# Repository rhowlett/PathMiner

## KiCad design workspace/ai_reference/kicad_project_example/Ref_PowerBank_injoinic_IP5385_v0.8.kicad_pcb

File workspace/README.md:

<!-- v0.1 -->
# PathMiner

DC resistance analysis for KiCad PCBs. Reads a `.kicad_pcb` — stackup, tracks, arcs, vias,
pads, filled zones — and answers *"what is the resistance from this pad to that pad, and does
the design pass?"*

It traces real routed copper into a resistor network, derives via barrel spans from the layers
that actually land on them (never from the via's declared layers), models stitched pours as
either a fast 1-D ladder or a rasterised mesh, and solves the whole net by nodal analysis so
parallel copper counts. Output is point-to-point resistance, voltage drop, endpoint voltage and
temperature rise, in Markdown, text, PDF or JSON, driven by a schema-validated JSON
net-selection file so the same audit re-runs from the CLI against every board revision.

## Status

**Working application, pre-split.** All functionality currently lives in the single file
`tools/pcb_trace_resistance.py` (v0.13, 5546 lines). The package folders `core/`, `ui/`,
`tests/` and `schema/` are scaffolded but empty; the split is designed in
`documents/library_refactor_recommendations.md` and has not been executed.

| Selftest | Result |
|---|---|
| Reference test board | 254 / 254 |
| Real 4-layer power bank | 284 / 284 |
| Headless, no board | 118 / 118 |

## Running it

```bash
python3 tools/pcb_trace_resistance.py                       # GUI
python3 tools/pcb_trace_resistance.py board.kicad_pcb       # GUI, board preloaded

python3 tools/pcb_trace_resistance.py --selftest [board.kicad_pcb]
python3 tools/pcb_trace_resistance.py --dump-stackup board.kicad_pcb [--plating 25] [--outer-plating]
python3 tools/pcb_trace_resistance.py --emit-schema [file.json]
python3 tools/pcb_trace_resistance.py --emit-nets board.kicad_pcb --out sel.json
python3 tools/pcb_trace_resistance.py --report board.kicad_pcb --nets sel.json \
        [--plating 18] [--zone-model none|ladder|mesh] [--mesh-pitch 0.25] \
        [--ambient 25] [--current 1] [--format md|txt|json] [--out FILE]
```

Requires **PySide6** for the GUI. `scipy` is optional and used automatically when present —
two to three orders of magnitude faster on meshed pours — with a pure-Python conjugate
gradient fallback when it is absent. The fallback is not optional going forward: a KiCad
plugin runs inside KiCad's bundled interpreter, where scipy may not exist.

## Tree

```
pathminer/
  core/                 business logic, no UI imports          (scaffolded, empty)
  ui/                   Qt layer                               (scaffolded, empty)
    tabs/ common/ dialogs/ themes/ widgets/
  tools/                dev and maintenance scripts
    pcb_trace_resistance.py     the working application, v0.13
  tests/                                                       (scaffolded, empty)
  schema/               data models, validation
    pcb_net_selection.schema.json
  ai_reference/
    code_samples/ doc_samples/ examples/
  documents/
    change_log.md
    via_tab_design_contract.md            the resistance model, D1-D8 closed
    library_refactor_recommendations.md   how to split this into a library, R1-R10
    path_capture_design.md                KiCad plugin + path JSON, D1-D10 closed
    help/ user_guides/
  README.md
```

## Documents

Read them in this order:

1. **`via_tab_design_contract.md`** — what the tool computes and why. Decisions D1–D8 with the
   evidence that closed them, the acceptance vectors, and the KiCad file-format gotchas found
   the hard way (layer ordinals are not stack order; a via's declared layers are the drilled
   barrel, not the current path; a zone fill is cut back around every pad it serves).
2. **`library_refactor_recommendations.md`** — R1–R10 for splitting this into a reusable
   package, with the measured evidence that the core has no Qt dependency and the case against
   writing C.
3. **`path_capture_design.md`** — the KiCad plugin, the path JSON schema, source and sink
   models, and D1–D10.

## Conventions

Per-file version tags on line 1 (line 2 after a shebang), Minor bumped on every change, one
change log at `documents/change_log.md`. Every delivery is a zip of this full tree. See
`documents/change_log.md` for the rules.

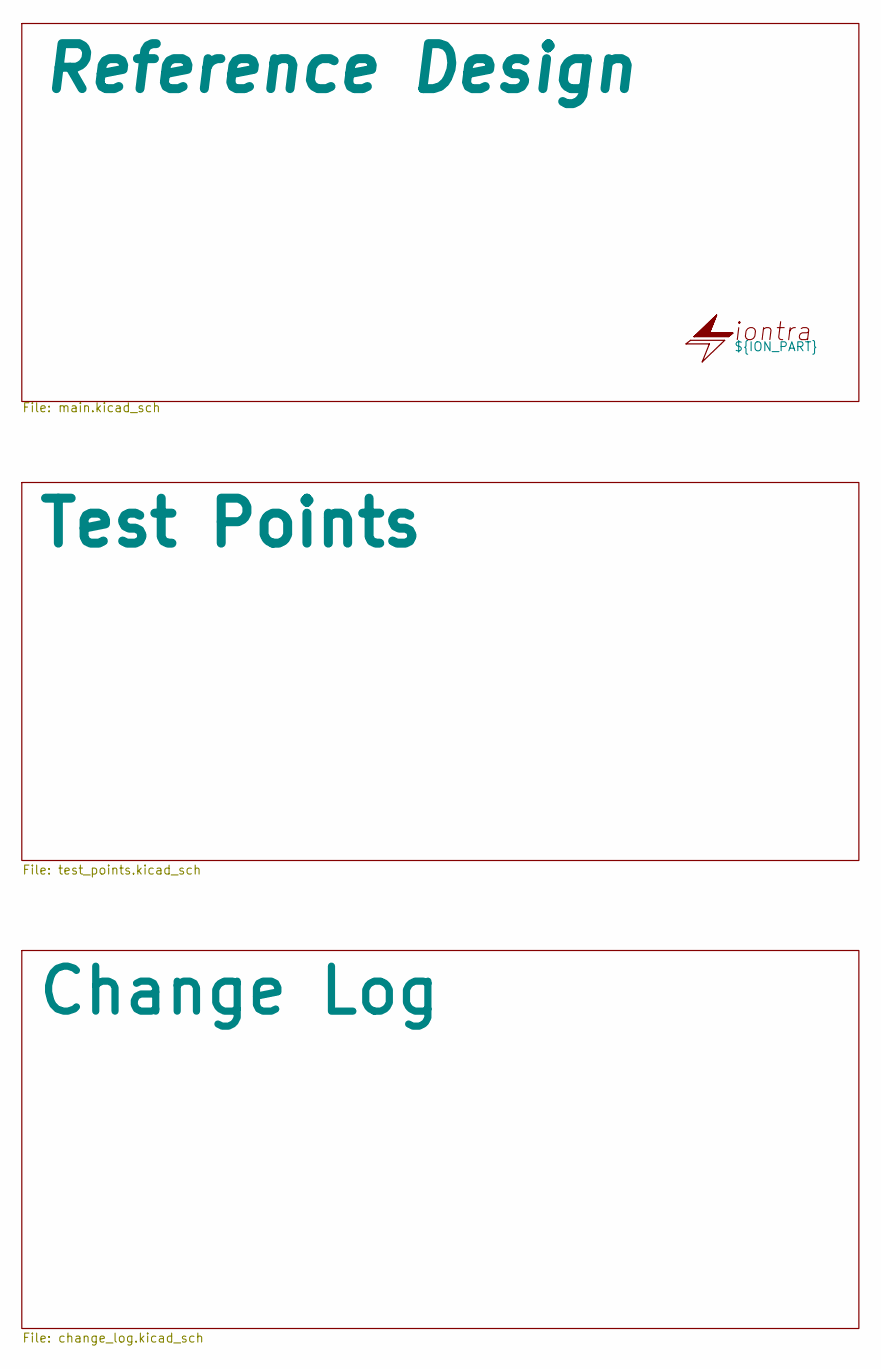
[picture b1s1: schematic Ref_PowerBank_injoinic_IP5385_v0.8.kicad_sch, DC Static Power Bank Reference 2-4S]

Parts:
ION101: ${ION_PART}; ION_LOGO

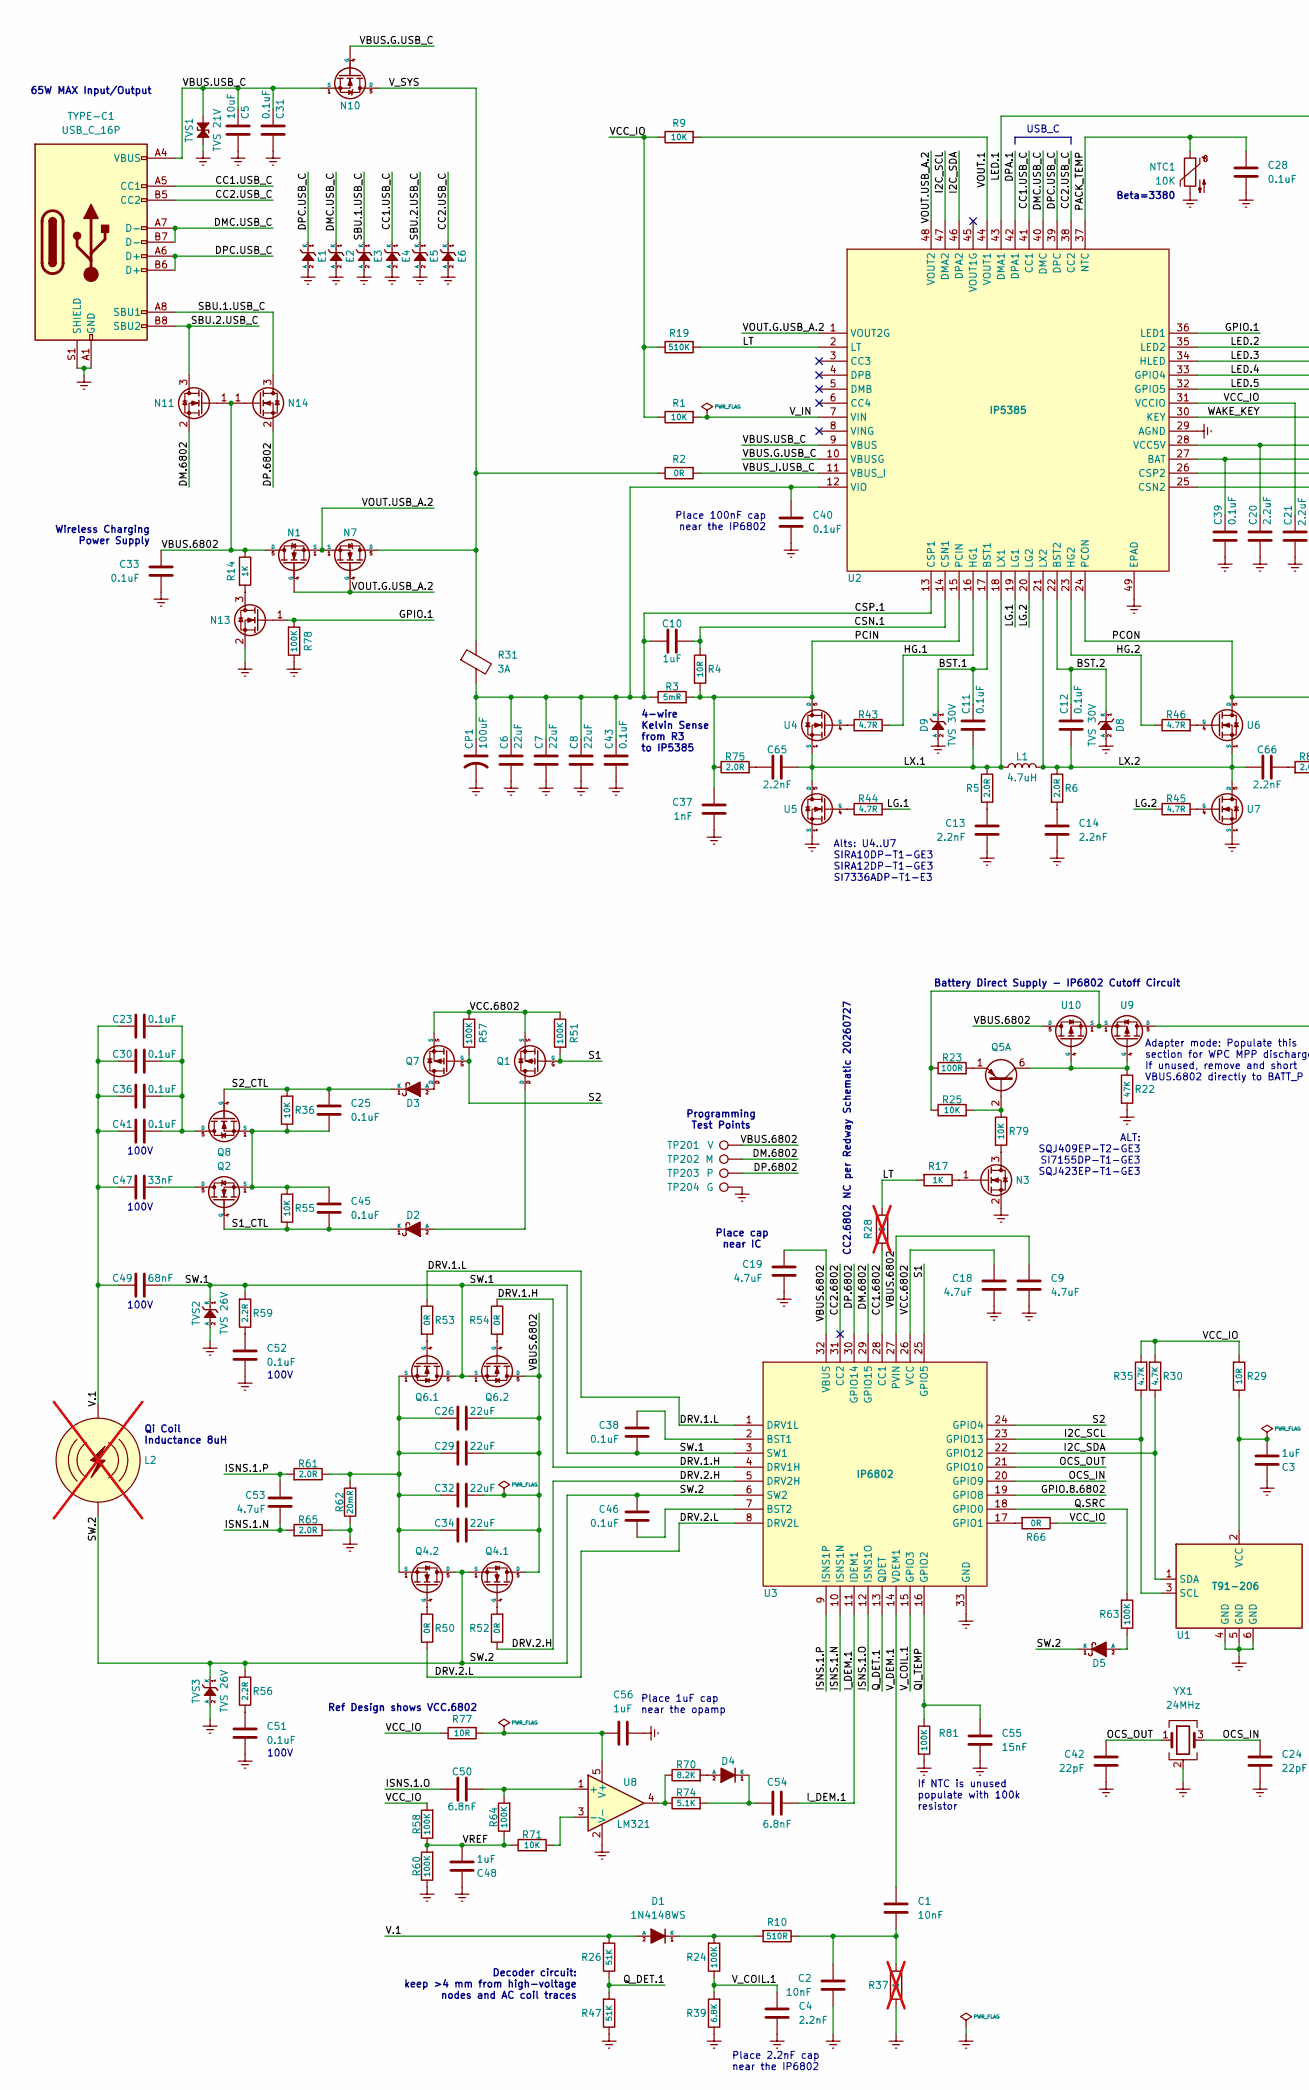
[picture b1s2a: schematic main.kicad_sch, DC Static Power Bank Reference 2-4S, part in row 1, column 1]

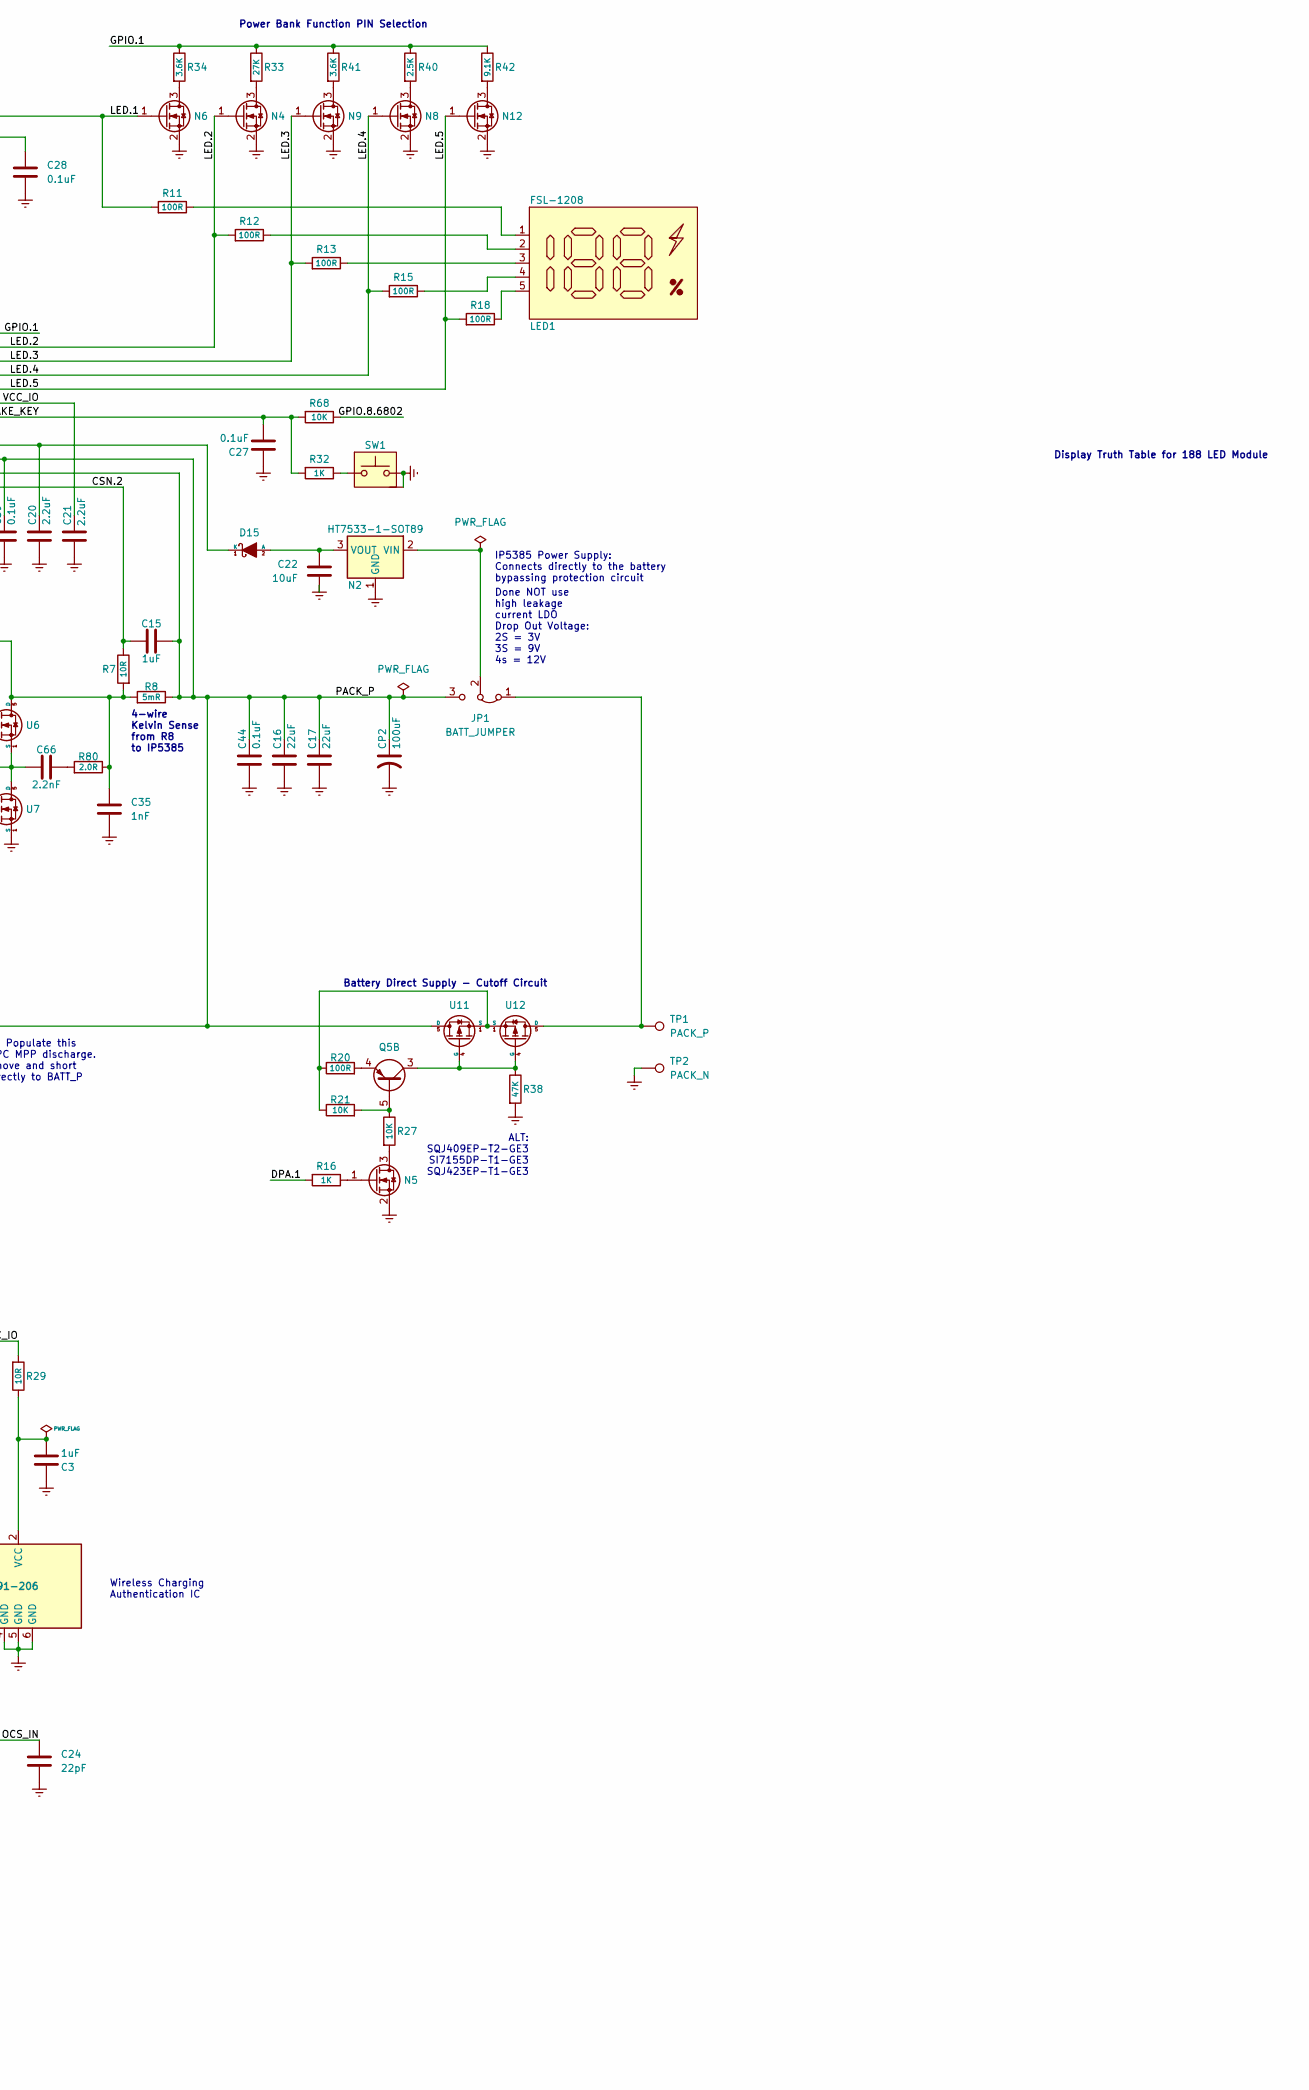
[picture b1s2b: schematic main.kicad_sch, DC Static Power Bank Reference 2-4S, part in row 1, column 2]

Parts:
C1, C2: 10nF; C_0402_1005Metric
C3, C10, C15, C48, C56: 1uF; C_0402_1005Metric
C4, C13, C14: 2.2nF; C_0402_1005Metric
C5, C22: 10uF; C_0805_2012Metric; Part # GRM21BZ71E106KE15K; Digikey 490-GRM21BZ71E106KE15KCT-ND
C6, C7, C8, C16, C17, C26, C29, C32, C34: 22uF; C_0805_2012Metric
C9, C18, C19, C53: 4.7uF; C_0805_2012Metric
C11, C12, C25, C27, C28, C31, C33, C38, C39, C40, C43, C44, C45, C46: 0.1uF; C_0402_1005Metric
C20, C21: 2.2uF; C_0603_1608Metric
C23, C30, C36, C41: 0.1uF; C_1206_3216Metric
C24, C42: 22pF; C_0402_1005Metric
C35, C37: 1nF; C_0402_1005Metric
C47: 33nF; C_1206_3216Metric
C49: 68nF; C_1206_3216Metric
C50, C54: 6.8nF; C_0402_1005Metric
C51, C52: 0.1uF; C_0603_1608Metric
C55: 15nF; C_0402_1005Metric
C65, C66: 2.2nF; C_0603_1608Metric
CP1, CP2: 100uF; CP_Elec_6.3x5.9
D1: 1N4148WS; D_SOD-323; Part # 1N4148WS,H3F(B; Digikey 264-1N4148WSH3F(BCT-ND
D2, D3, D4, D5, D15: 1N5819WS; D_SOD-323; Part # 1N5819WS; Digikey 5399-1N5819WSCT-ND
D8, D9: TVS 30V; D_SOD-323; Part # SLNC3D15V1B; Digikey 5399-SLNC3D15V1BCT-ND
E1, E2, E3, E4, E5, E6: TVS 5.5V; D_0402; Part # UCLAMP5581P.F; Digikey 600-UCLAMP5581P.FCT-ND
JP1: BATT_JUMPER; SolderJumper-3_P2.0mm_Open_TrianglePad1.0x1.5mm_NumberLabels
L1: 4.7uH; L_Wurth_WE-LHMI-8040_PW3; Part # 74437358047; Digikey 732-7210-1-ND
L2: TBD; L_Qi2.2_P5mm; not fitted
LED1: FSL-1208; Part # FSL- 1208; Digikey NA
N1, N7, N10: BSC028N06LS3; PG-TDSON-8-1; Part # BSC028N06LS3GATMA1; Digikey BSC028N06LS3GATMA1CT-ND
N2: HT7533-1-SOT89; SOT-89-3; Part # HT7533-1; Digikey 4518-HT7533-1CT-ND
N3, N4, N5, N6, N8, N9, N11, N12, N13, N14: 2N7002; SOT-523; Part # 2N7002KT; Digikey 5399-2N7002KTCT-ND
NTC1: 10K; R_0603_1608Metric
Q1, Q7: AO3401A; SOT-23-3; Part # AO3401A; Digikey 785-1001-1-ND
Q2, Q8: BSC028N06LS3; PG-TDSON-8-1; Part # BSC028N06LS3GATMA1; Digikey BSC028N06LS3GATMA1CT-ND
Q4.1, Q4.2, Q6.1, Q6.2: SIRA14DP; SIRA14DPT1GE3; Part # SIRA14DP-T1-GE3; Digikey SIRA14DP-T1-GE3CT-ND
Q5: FFB3906; SOT-363_SC-70-6; Digikey MBT3906DW1T1GOSCT-ND
R1, R9, R21, R25, R27, R36, R55, R68, R71, R79: 10K; R_0402_1005Metric
R2, R50, R52, R53, R54, R66: 0R; R_0402_1005Metric
R3, R8: 5mR; R_1206_3216Metric
R4, R7, R29, R77: 10R; R_0402_1005Metric
R5, R6, R61, R65, R75, R80: 2.0R; R_0402_1005Metric
R10: 510R; R_0402_1005Metric
R11, R12, R13, R15, R18, R20, R23: 100R; R_0402_1005Metric
R14, R16, R17, R32: 1K; R_0402_1005Metric
R19: 510K; R_0402_1005Metric
R22, R38: 47K; R_0402_1005Metric
R24, R51, R57, R58, R60, R63, R64, R78, R81: 100K; R_0402_1005Metric
R26, R47: 51K; R_0402_1005Metric
R28, R37: 0; R_0402_1005Metric; not fitted
R30, R35: 4.7K; R_0402_1005Metric
R31: 3A; R_1206_3216Metric
R33: 27K; R_0402_1005Metric
R34, R41: 3.6K; R_0402_1005Metric
R39: 6.8K; R_0402_1005Metric
R40: 2.5K; R_0402_1005Metric
R42: 9.1K; R_0402_1005Metric
R43, R44, R45, R46: 4.7R; R_0402_1005Metric
R56, R59: 2.2R; R_0603_1608Metric
R62: 20mR; R_1206_3216Metric
R70: 8.2K; R_0402_1005Metric
R74: 5.1K; R_0402_1005Metric
SW1: SW_Push; TS36CA06250gf031; Part # TS36CA-0.6 250gf 031
TP1: PACK_P; SolderWirePad_1x01_SMD_1.5x3mm
TP2: PACK_N; SolderWirePad_1x01_SMD_1.5x3mm
TP201: V; TestPoint_Pad_D1.0mm
TP202: M; TestPoint_Pad_D1.0mm
TP203: P; TestPoint_Pad_D1.0mm
TP204: G; TestPoint_Pad_D1.0mm
TVS1: TVS 21V; SOD-963 CST2C_TOS; Part # DF2S23P2CTC,L3F; Digikey DF2S23P2CTCL3FCT-ND
TVS2, TVS3: TVS 26V; D_SOD-523; Part # XCEZ12V,L3XHF; Digikey 264-XCEZ12VL3XHFCT-ND
TYPE-C1: USB_C_16P; SAMESKY_UJ20-C-H-G-SMT-1-P16-TR; Part # UJ20-C-H-G-SMT-1-P16-TR; Digikey 2223-UJ20-C-H-G-SMT-1-P16-TRCT-ND
U1: T91-206; DFN-6_1.3x1.2mm_P0.4mm; Part # T91-206-Q; JLCPCB C9900260572
U2: IP5385; QFN-48-1EP_6x6mm_P0.4mm_EP4.2x4.2mm; Part # IP5385; Digikey NA
U3: IP6802; QFN-32-1EP_5x5mm_P0.5mm_EP3.3x3.3mm; Part # IP6802; Digikey NA
U4, U5, U6, U7: SIRA14DP; SIRA14DPT1GE3; Part # SIRA14DP-T1-GE3; Digikey SIRA14DP-T1-GE3CT-ND
U8: LM321; SOT-23-5
U9, U10, U11, U12: SQJ409EP; SQJ409EP-T2_GE3; Part # SQJ409EP-T2_GE3; Digikey 742-SQJ409EP-T2_GE3CT-ND
YX1: 24MHz; OSC_4P_3.2x2.5mm; Part # SXT32422AA16-24.000M; Digikey 2388-SXT32422AA16-24.000M-ND

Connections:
/Reference Design/BST.1: C11.1, D9.1 (K), U2.17 (BST1)
/Reference Design/BST.2: C12.1, D8.1 (K), U2.22 (BST2)
/Reference Design/CC1.6802: R28.1, U3.28 (CC1)
/Reference Design/CC1.USB_C: E4.1 (K), TYPE-C1.A5 (CC1), U2.41 (CC1)
/Reference Design/CC2.6802: U3.31 (CC2)
/Reference Design/CC2.USB_C: E6.1 (K), TYPE-C1.B5 (CC2), U2.38 (CC2)
/Reference Design/CSN.1: C10.2, R4.1, U2.14 (CSN1)
/Reference Design/CSN.2: C15.2, R7.1, U2.25 (CSN2)
/Reference Design/CSP.1: C6.1, C7.1, C8.1, C10.1, C40.1, C43.1, CP1.1, R3.1, R31.2, U2.12 (VIO), U2.13 (CSP1)
/Reference Design/DM.6802: N11.2 (S), TP202.1, U3.29 (GPIO15)
/Reference Design/DMC.USB_C: E2.1 (K), TYPE-C1.A7 (D-), TYPE-C1.B7 (D-), U2.40 (DMC)
/Reference Design/DP.6802: N14.2 (S), TP203.1, U3.30 (GPIO14)
/Reference Design/DPA.1: R16.2, U2.42 (DPA1)
/Reference Design/DPC.USB_C: E1.1 (K), TYPE-C1.A6 (D+), TYPE-C1.B6 (D+), U2.39 (DPC)
/Reference Design/DRV.1.H: R54.1, U3.4 (DRV1H)
/Reference Design/DRV.1.L: R53.1, U3.1 (DRV1L)
/Reference Design/DRV.2.H: R52.1, U3.5 (DRV2H)
/Reference Design/DRV.2.L: R50.1, U3.8 (DRV2L)
/Reference Design/GPIO.1: N13.1 (G), R33.1, R34.1, R40.1, R41.1, R42.1, R78.2, U2.36 (LED1)
/Reference Design/GPIO.8.6802: R68.1, U3.19 (GPIO8)
/Reference Design/HG.1: R43.2, U2.16 (HG1)
/Reference Design/HG.2: R46.1, U2.23 (HG2)
/Reference Design/I2C_SCL: R35.1, U1.3 (SCL), U2.47 (DMA2), U3.23 (GPIO13)
/Reference Design/I2C_SDA: R30.1, U1.1 (SDA), U2.46 (DPA2), U3.22 (GPIO12)
/Reference Design/ISNS.1.N: C53.1, R65.2, U3.10 (ISNS1N)
/Reference Design/ISNS.1.O: C50.1, U3.12 (ISNS1O)
/Reference Design/ISNS.1.P: C53.2, R61.2, U3.9 (ISNS1P)
/Reference Design/I_DEM.1: C54.2, U3.11 (IDEM1)
/Reference Design/LED.1: N6.1 (G), R11.2, U2.43 (DMA1)
/Reference Design/LED.2: N4.1 (G), R12.2, U2.35 (LED2)
/Reference Design/LED.3: N9.1 (G), R13.2, U2.34 (HLED)
/Reference Design/LED.4: N8.1 (G), R15.2, U2.33 (GPIO4)
/Reference Design/LED.5: N12.1 (G), R18.2, U2.32 (GPIO5)
/Reference Design/LG.1: R44.2, U2.19 (LG1)
/Reference Design/LG.2: R45.1, U2.20 (LG2)
/Reference Design/LT: R17.2, R19.2, R28.2, U2.2 (LT)
/Reference Design/LX.1: C11.2, C65.2, L1.1, R5.1, U2.18 (LX1), U4.1 (S), U4.2 (S), U4.3 (S), U5.5 (D)
/Reference Design/LX.2: C12.2, C66.2, L1.2, R6.1, U2.21 (LX2), U6.1 (S), U6.2 (S), U6.3 (S), U7.5 (D)
/Reference Design/OCS_IN: C24.1, U3.20 (GPIO9), YX1.3
/Reference Design/OCS_OUT: C42.1, U3.21 (GPIO10), YX1.1
/Reference Design/PACK_P: C15.1, C16.1, C17.1, C39.2, C44.1, CP2.1, JP1.3 (B), R8.1, U2.26 (CSP2), U2.27 (BAT), U9.5 (D), U11.5 (D)
/Reference Design/PACK_TEMP: C28.1, NTC1.1, U2.37 (NTC)
/Reference Design/PCIN: C37.2, R3.2, R4.2, R75.1, U2.15 (PCIN), U4.5 (D)
/Reference Design/PCON: C35.2, R7.2, R8.2, R80.1, U2.24 (PCON), U6.5 (D)
/Reference Design/Q.SRC: R63.2, U3.18 (GPIO0)
/Reference Design/QI_TEMP: C55.1, R81.1, U3.16 (GPIO2)
/Reference Design/Q_DET.1: R26.1, R47.2, U3.13 (QDET)
/Reference Design/S1: Q1.G, R51.2, U3.25 (GPIO5)
/Reference Design/S1_CTL: C45.2, D2.1 (K), Q2.4 (G), R55.1
/Reference Design/S2: Q7.G, R57.2, U3.24 (GPIO4)
/Reference Design/S2_CTL: C25.1, D3.1 (K), Q8.4 (G), R36.2
/Reference Design/SBU.1.USB_C: E3.1 (K), N14.3 (D), TYPE-C1.A8 (SBU1)
/Reference Design/SBU.2.USB_C: E5.1 (K), N11.3 (D), TYPE-C1.B8 (SBU2)
/Reference Design/SW.1: C38.1, C49.2, Q6.1.5 (D), Q6.2.1 (S), Q6.2.2 (S), Q6.2.3 (S), R59.2, TVS2.1 (K), U3.3 (SW1)
/Reference Design/SW.2: C46.2, D5.1 (K), L2.2, Q4.1.1 (S), Q4.1.2 (S), Q4.1.3 (S), Q4.2.5 (D), R56.2, TVS3.1 (K), U3.6 (SW2)
/Reference Design/V.1: C23.1, C30.1, C36.1, C41.1, C47.1, C49.1, D1.2 (A), L2.1, R26.2
/Reference Design/VBUS.6802: C9.1, C19.1, C26.2, C29.2, C32.2, C33.1, C34.2, N1.5 (D), N11.1 (G), N14.1 (G), Q4.1.5 (D), Q6.2.5 (D), R14.1, TP201.1, U3.27 (PVIN), U3.32 (VBUS), U10.5 (D)
/Reference Design/VBUS.G.USB_C: N10.4 (G), U2.10 (VBUSG)
/Reference Design/VBUS.USB_C: C5.1, C31.1, N10.1 (S), N10.2 (S), N10.3 (S), TVS1.1 (A1), TYPE-C1.A4 (VBUS), TYPE-C1.A9 (VBUS), TYPE-C1.B4 (VBUS), TYPE-C1.B9 (VBUS), U2.9 (VBUS)
/Reference Design/VBUS_I.USB_C: R2.2, U2.11 (VBUS_I)
/Reference Design/VCC.6802: C18.1, Q1.S, Q7.S, R51.1, R57.1, U3.26 (VCC)
/Reference Design/VCC_IO: C21.2, R1.1, R9.1, R19.1, R29.2, R30.2, R35.2, R58.2, R66.1, R77.1, U2.31 (VCCIO)
/Reference Design/VOUT.1: R9.2, U2.44 (VOUT1)
/Reference Design/VOUT.G.USB_A.2: N1.4 (G), N7.4 (G), U2.1 (VOUT2G)
/Reference Design/VOUT.USB_A.2: N1.1 (S), N1.2 (S), N1.3 (S), N7.1 (S), N7.2 (S), N7.3 (S), U2.48 (VOUT2)
/Reference Design/VREF: C48.1, R58.1, R60.2, R64.1, R71.1
/Reference Design/V_COIL.1: C4.1, R24.1, R39.2, U3.15 (GPIO3)
/Reference Design/V_DEM.1: C1.1, U3.14 (VDEM1)
/Reference Design/V_IN: R1.2, U2.7 (VIN)
/Reference Design/V_SYS: N7.5 (D), N10.5 (D), R2.1, R31.1
/Reference Design/WAKE_KEY: C27.1, R32.2, R68.2, U2.30 (KEY)
GNDREF: C2.2, C3.1, C4.2, C5.2, C6.2, C7.2, C8.2, C9.2, C13.2, C14.2, C16.2, C17.2, C18.2, C19.2, C20.2, C21.1, C22.2, C24.2, C27.2, C28.2, C31.2, C33.2, C35.1, C37.1, C39.1, C40.2, C42.2, C43.2, C44.2, C48.2, C51.2, C52.2, C55.2, C56.2, CP1.2, CP2.2, D8.2 (A), D9.2 (A), E1.2 (A), E2.2 (A), E3.2 (A), E4.2 (A), E5.2 (A), E6.2 (A), N2.1 (GND), N3.2 (S), N4.2 (S), N5.2 (S), N6.2 (S), N8.2 (S), N9.2 (S), N12.2 (S), N13.2 (S), NTC1.2, R22.2, R37.1, R38.2, R39.1, R47.1, R60.1, R62.1, R65.1, R78.1, R81.2, SW1.2, SW1.MP1 (Mount), TP2.1, TP204.1, TVS1.2 (A2), TVS2.2 (A), TVS3.2 (A), TYPE-C1.A1 (GND), TYPE-C1.A12 (GND), TYPE-C1.B1 (GND), TYPE-C1.B12 (GND), TYPE-C1.S1 (SHIELD), U1.4 (GND), U1.5 (GND), U1.6 (GND), U2.29 (AGND), U2.49 (EPAD), U3.33 (GND), U5.1 (S), U5.2 (S), U5.3 (S), U7.1 (S), U7.2 (S), U7.3 (S), U8.2 (V-), YX1.2 (G), YX1.4 (G)
unnamed: C1.2, C2.1, R10.1, R37.2
unnamed: C13.1, R5.2
unnamed: C14.1, R6.2
unnamed: C25.2, C45.1, Q2.1 (S), Q2.2 (S), Q2.3 (S), Q8.1 (S), Q8.2 (S), Q8.3 (S), R36.1, R55.2
unnamed: C26.1, C29.1, C32.1, C34.1, Q4.2.1 (S), Q4.2.2 (S), Q4.2.3 (S), Q6.1.1 (S), Q6.1.2 (S), Q6.1.3 (S), R61.1, R62.2
unnamed: C51.1, R56.1
unnamed: C52.1, R59.1
unnamed: C65.1, R75.2
unnamed: C66.1, R80.2
unnamed: D1.1 (K), R10.2, R24.2
unnamed: D2.2 (A), Q1.D
unnamed: D3.2 (A), Q7.D
unnamed: D4.2 (A), R70.2
unnamed: C54.1, D4.1 (K), R74.2
unnamed: D5.2 (A), R63.1
unnamed: C22.1, D15.2 (A), N2.3 (VOUT)
unnamed: C20.1, D15.1 (K), U2.28 (VCC5V)
unnamed: JP1.1 (A), TP1.1, U12.5 (D)
unnamed: JP1.2 (C), N2.2 (VIN)
unnamed: LED1.2 (1), R12.1
unnamed: LED1.3 (1), R13.1
unnamed: LED1.4 (1), R15.1
unnamed: LED1.5 (1), R18.1
unnamed: LED1.1, R11.1
unnamed: N3.3 (D), R79.2
unnamed: N3.1 (G), R17.1
unnamed: N4.3 (D), R33.2
unnamed: N5.3 (D), R27.2
unnamed: N5.1 (G), R16.1
unnamed: N6.3 (D), R34.2
unnamed: N8.3 (D), R40.2
unnamed: N9.3 (D), R41.2
unnamed: N12.3 (D), R42.2
unnamed: N13.3 (D), R14.2
unnamed: C47.2, Q2.5 (D)
unnamed: Q4.1.4 (G), R52.2
unnamed: Q4.2.4 (G), R50.2
unnamed: Q5.2 (B1), R25.2, R79.1
unnamed: Q5.6 (C1), R22.1, U9.4 (G), U10.4 (G)
unnamed: Q5.1 (E1), R23.2
unnamed: Q5.5 (B2), R21.2, R27.1
unnamed: Q5.3 (C2), R38.1, U11.4 (G), U12.4 (G)
unnamed: Q5.4 (E2), R20.2
unnamed: Q6.1.4 (G), R53.2
unnamed: Q6.2.4 (G), R54.2
unnamed: C23.2, C30.2, C36.2, C41.2, Q8.5 (D)
unnamed: R20.1, R21.1, U11.1 (S), U11.2 (S), U11.3 (S), U12.1 (S), U12.2 (S), U12.3 (S)
unnamed: R23.1, R25.1, U9.1 (S), U9.2 (S), U9.3 (S), U10.1 (S), U10.2 (S), U10.3 (S)
unnamed: R32.1, SW1.1
unnamed: R70.1, R74.1, U8.4
unnamed: C3.2, R29.1, U1.2 (VCC)
unnamed: C38.2, U3.2 (BST1)
unnamed: C46.1, U3.7 (BST2)
unnamed: R66.2, U3.17 (GPIO1)
unnamed: R43.1, U4.4 (G)
unnamed: R44.1, U5.4 (G)
unnamed: R46.2, U6.4 (G)
unnamed: R45.2, U7.4 (G)
unnamed: C50.2, R64.2, U8.1 (+)
unnamed: R71.2, U8.3 (-)
unnamed: C56.1, R77.2, U8.5 (V+)

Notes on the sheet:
Decoder circuit: keep >4 mm from high-voltage nodes and AC coil traces
IP5385 Power Supply: Connects directly to the battery bypassing protection circuit
4-wire Kelvin Sense from R3 to IP5385
Place 2.2nF cap near the IP6802
Wireless Charging Authentication IC
Place 1uF cap near the opamp
Alts: U4..U7 SIRA10DP-T1-GE3 SIRA12DP-T1-GE3 SI7336ADP-T1-E3
100V
Qi Coil Inductance 8uH
Battery Direct Supply - Cutoff Circuit
4-wire Kelvin Sense from R8 to IP5385
Battery Direct Supply - IP6802 Cutoff Circuit
Place cap near IC
CC2.6802 NC per Redway Schematic 20260727
Wireless Charging Power Supply
Ref Design shows VCC.6802
Programming Test Points
Beta=3380
65W MAX Input/Output
Done NOT use high leakage current LDO Drop Out Voltage: 2S = 3V 3S = 9V 4s = 12V
ALT: SQJ409EP-T2-GE3 SI7155DP-T1-GE3 SQJ423EP-T1-GE3
Place 100nF cap near the IP6802
USB_C
If NTC is unused populate with 100k resistor
Power Bank Function PIN Selection
Adapter mode: Populate this section for WPC MPP discharge. If unused, remove and short VBUS.6802 directly to BATT_P
Display Truth Table for 188 LED Module

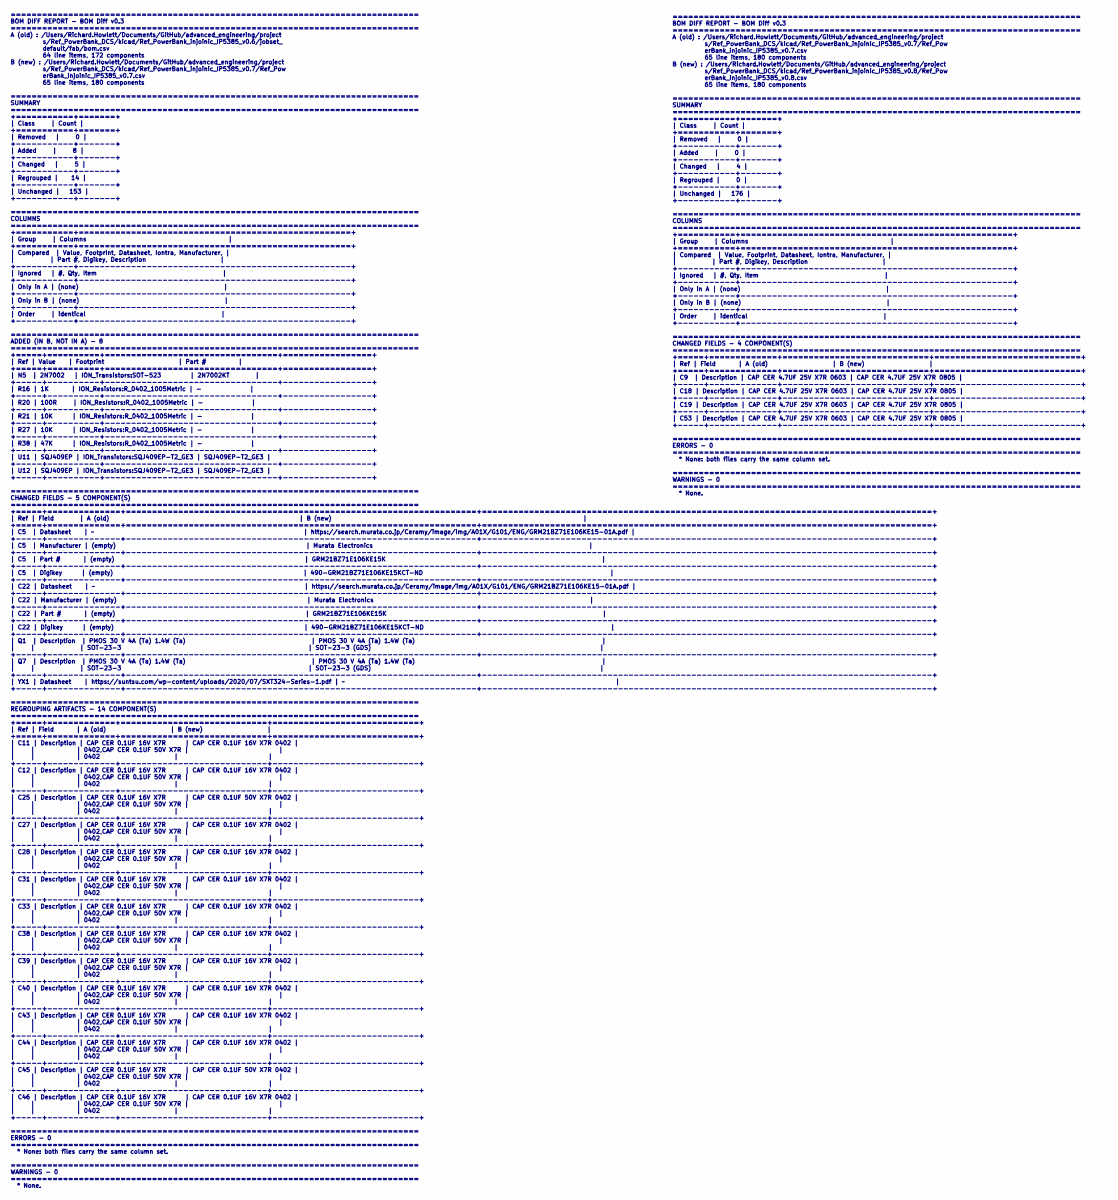
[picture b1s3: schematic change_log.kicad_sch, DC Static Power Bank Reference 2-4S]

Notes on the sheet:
============================================================================== BOM DIFF REPORT - BOM Diff v0.3 ============================================================================== A (old) : /Users/Richard.Howlett/Documents/GitHub/advanced_engineering/project s/Ref_PowerBank_DCS/kicad/Ref_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
============================================================================== BOM DIFF REPORT - BOM Diff v0.3 ============================================================================== A (old) : /Users/Richard.Howlett/Documents/GitHub/advanced_engineering/project s/Ref_PowerBank_DCS/kicad/Ref_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

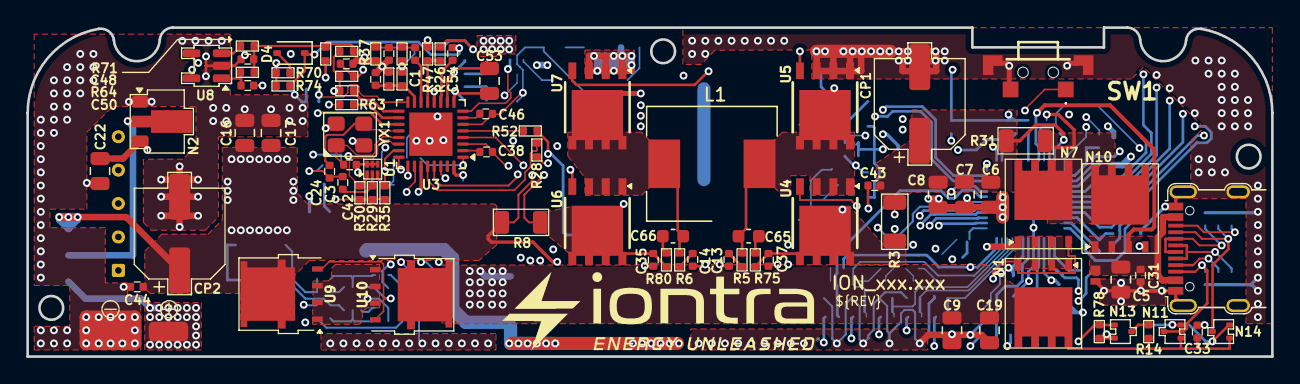
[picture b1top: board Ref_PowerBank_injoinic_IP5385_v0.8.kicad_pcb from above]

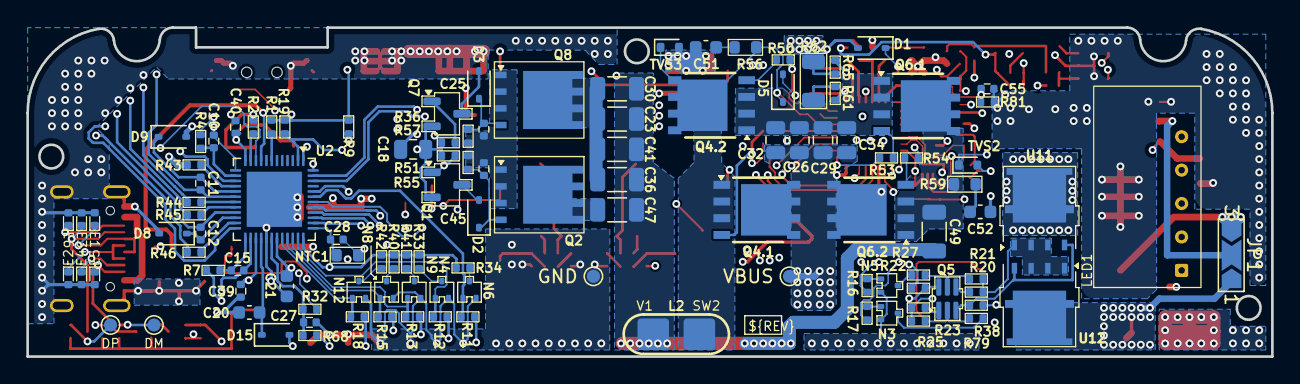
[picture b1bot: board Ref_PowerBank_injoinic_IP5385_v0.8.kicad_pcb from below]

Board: 4 copper layers, 94.6 x 25.0 mm, 201 parts (113 on the bottom side), 132 nets.
